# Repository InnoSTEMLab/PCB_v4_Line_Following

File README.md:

# PCB_v5_Line_Following

## Updates:
- New IC Atemga328pa -> Atemga32u4. Takes D+ and D- from usb no need for usb to uart controller
- Motor connectors moved in one section of the board
- Trace fixed for switch that was keeping motor controller on all the time. Motors will be off when usb c connected only.
- Power conversion only happens in one part of the pcb
- USB C footprint updated to current part we have previosuily ordered. No more issues soldering them.
- Decoupling capacitors added to motor driver and termination resistors to USB C data lines

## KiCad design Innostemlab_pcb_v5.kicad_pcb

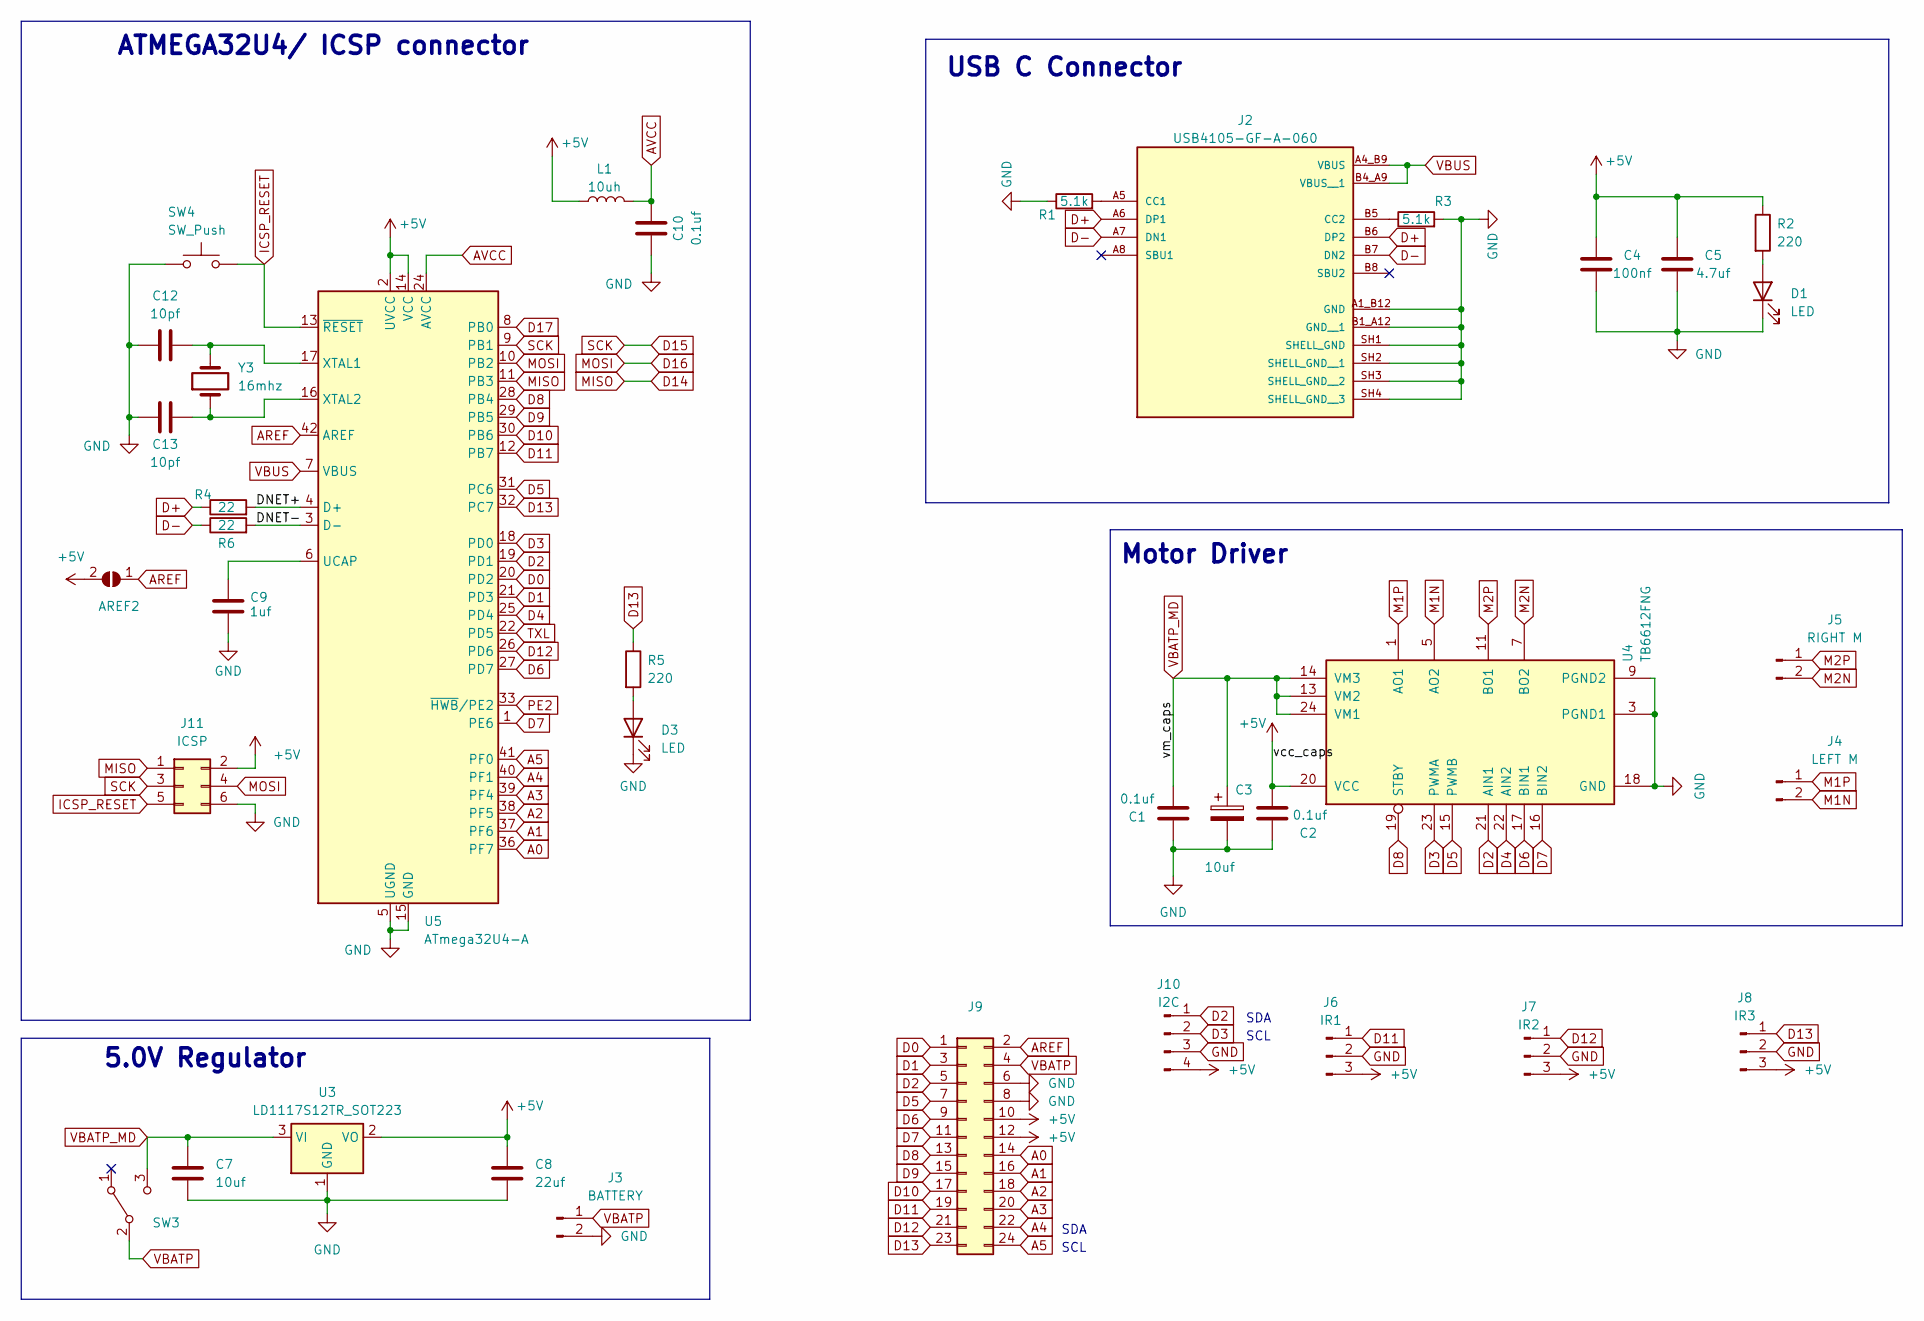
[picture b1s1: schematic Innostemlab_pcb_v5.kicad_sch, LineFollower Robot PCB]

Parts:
AREF2: SolderJumper_2_Open; SolderJumper-2_P1.3mm_Open_RoundedPad1.0x1.5mm
C1, C2, C10: 0.1uf; C_0805_2012Metric_Pad1.18x1.45mm_HandSolder
C3: 10uf; CP_EIA-3528-12_Kemet-T
C4: 100nf; C_0805_2012Metric_Pad1.18x1.45mm_HandSolder
C5: 4.7uf; C_0805_2012Metric_Pad1.18x1.45mm_HandSolder
C7: 10uf; C_0805_2012Metric_Pad1.18x1.45mm_HandSolder
C8: 22uf; C_0805_2012Metric_Pad1.18x1.45mm_HandSolder
C9: 1uf; C_0805_2012Metric_Pad1.18x1.45mm_HandSolder
C12, C13: 10pf; C_0805_2012Metric_Pad1.18x1.45mm_HandSolder
D1, D3: LED; LED_0805_2012Metric_Pad1.15x1.40mm_HandSolder
J2: USB4105-GF-A-060; GCT_USB4105-GF-A-060; PARTREV B3
J3: BATTERY; JST_EH_B2B-EH-A_1x02_P2.50mm_Vertical
J4: LEFT M; JST_EH_B2B-EH-A_1x02_P2.50mm_Vertical
J5: RIGHT M; JST_EH_B2B-EH-A_1x02_P2.50mm_Vertical
J6: IR1; PinHeader_1x03_P2.54mm_Vertical
J7: IR2; PinHeader_1x03_P2.54mm_Vertical
J8: IR3; PinHeader_1x03_P2.54mm_Vertical
J9: Conn_02x12_Odd_Even; PinHeader_2x12_P2.54mm_Vertical
J10: I2C; PinHeader_1x04_P2.54mm_Vertical
J11: ICSP; PinHeader_2x03_P2.54mm_Vertical
L1: 10uh; L_0805_2012Metric
R1, R3: 5.1k; R_0805_2012Metric_Pad1.20x1.40mm_HandSolder
R2, R5: 220; R_0805_2012Metric_Pad1.20x1.40mm_HandSolder
R4, R6: 22; R_0805_2012Metric_Pad1.20x1.40mm_HandSolder
SW3: SW_SPDT; SW_SLW-121586-5A-D
SW4: SW_Push; SW_TS09-63-25-WT-260-SMT-TR
U3: LD1117S12TR_SOT223; SOT-223-3_TabPin2
U4: TB6612FNG; SSOP-24_5.3x8.2mm_P0.65mm
U5: ATmega32U4-A; TQFP-44_10x10mm_P0.8mm
Y3: 16mhz; Crystal_HC49-4H_Vertical

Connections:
+5V: AREF2.2 (B), C2.2, C4.2, C5.2, C8.1, J6.3, J7.3, J8.3, J9.10, J9.12, J10.4, J11.2, L1.1, R2.1, U3.2 (VO), U4.20 (VCC), U5.2 (UVCC), U5.14 (VCC), U5.34 (VCC)
/DNET+: R4.2, U5.4 (D+)
/DNET-: R6.2, U5.3 (D-)
A0: J9.14, U5.36 (PF7)
A1: J9.16, U5.37 (PF6)
A2: J9.18, U5.38 (PF5)
A3: J9.20, U5.39 (PF4)
A4: J9.22, U5.40 (PF1)
A5: J9.24, U5.41 (PF0)
AREF: AREF2.1 (A), J9.2, U5.42 (AREF)
AVCC: C10.2, L1.2, U5.24 (AVCC), U5.44 (AVCC)
D0: J9.1, U5.20 (PD2)
D1: J9.3, U5.21 (PD3)
D2: J9.5, J10.1, U4.21 (AIN1), U5.19 (PD1)
D3: J10.2, U4.23 (PWMA), U5.18 (PD0)
D4: U4.22 (AIN2), U5.25 (PD4)
D5: J9.7, U4.15 (PWMB), U5.31 (PC6)
D6: J9.9, U4.17 (BIN1), U5.27 (PD7)
D7: J9.11, U4.16 (BIN2), U5.1 (PE6)
D8: J9.13, U4.19 (STBY), U5.28 (PB4)
D9: J9.15, U5.29 (PB5)
D10: J9.17, U5.30 (PB6)
D11: J6.1, J9.19, U5.12 (PB7)
D12: J7.1, J9.21, U5.26 (PD6)
D13: J8.1, J9.23, R5.1, U5.32 (PC7)
D14: J11.1, U5.11 (PB3)
D15: J11.3, U5.9 (PB1)
D16: J11.4, U5.10 (PB2)
D17: U5.8 (PB0)
D+: J2.A6 (DP1), J2.B6 (DP2), R4.1
D-: J2.A7 (DN1), J2.B7 (DN2), R6.1
GND: C1.1, C2.1, C3.2, C4.1, C5.1, C7.2, C8.2, C9.1, C10.1, C12.1, C13.1, D1.1 (K), D3.1 (K), J2.A1_B12 (GND), J2.B1_A12 (GND__1), J2.SH1 (SHELL_GND), J2.SH2 (SHELL_GND__1), J2.SH3 (SHELL_GND__2), J2.SH4 (SHELL_GND__3), J3.2, J6.2, J7.2, J8.2, J9.6, J9.8, J10.3, J11.6, R1.1, R3.2, SW4.1, U3.1 (GND), U4.3 (PGND1), U4.4 (PGND1), U4.9 (PGND2), U4.10 (PGND2), U4.18 (GND), U5.5 (UGND), U5.15 (GND), U5.23 (GND), U5.35 (GND), U5.43 (GND)
ICSP_RESET: J11.5, SW4.2, U5.13 (~RESET)
M1N: J4.2, U4.5 (AO2), U4.6 (AO2)
M1P: J4.1, U4.1 (AO1), U4.2 (AO1)
M2N: J5.2, U4.7 (BO2), U4.8 (BO2)
M2P: J5.1, U4.11 (BO1), U4.12 (BO1)
unnamed: D1.2 (A), R2.2
unnamed: D3.2 (A), R5.2
unnamed: J2.A5 (CC1), R1.2
unnamed: J2.B5 (CC2), R3.1
unnamed: C9.2, U5.6 (UCAP)
unnamed: C12.2, U5.17 (XTAL1), Y3.2
unnamed: C13.2, U5.16 (XTAL2), Y3.1
PE2: U5.33 (~HWB/PE2)
TXL: U5.22 (PD5)
VBATP: J3.1, J9.4, SW3.2 (B)
VBATP_MD: C1.2, C3.1, C7.1, SW3.3 (C), U3.3 (VI), U4.13 (VM2), U4.14 (VM3), U4.24 (VM1)
VBUS: J2.A4_B9 (VBUS), J2.B4_A9 (VBUS__1), U5.7 (VBUS)

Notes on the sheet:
USB C Connector
SCL
SDA
ATMEGA32U4/ ICSP connector
5.0V Regulator
Motor Driver

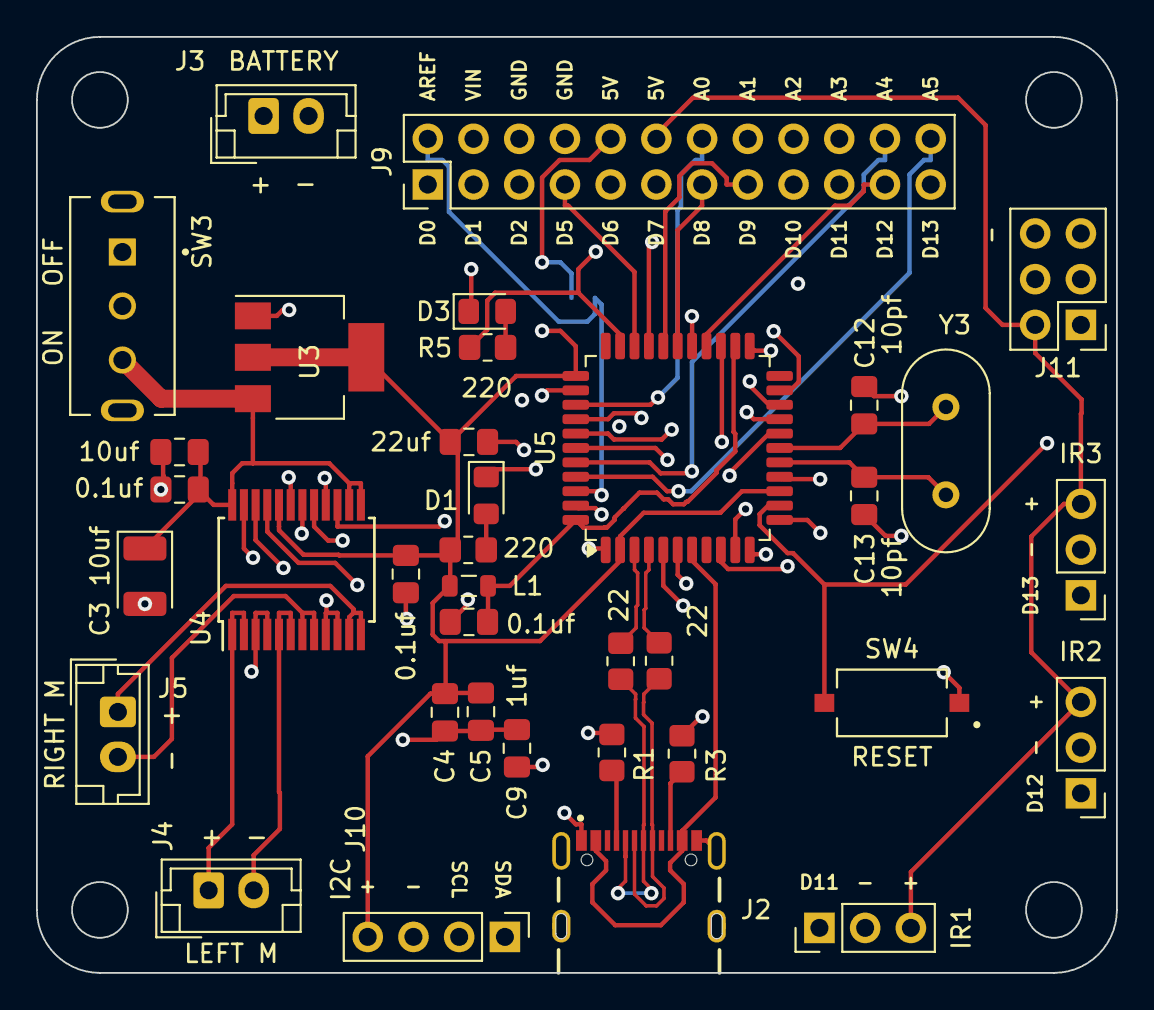
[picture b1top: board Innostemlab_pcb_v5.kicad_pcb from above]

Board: 4 copper layers, 60.0 x 52.0 mm, 37 parts (1 on the bottom side), 46 nets.

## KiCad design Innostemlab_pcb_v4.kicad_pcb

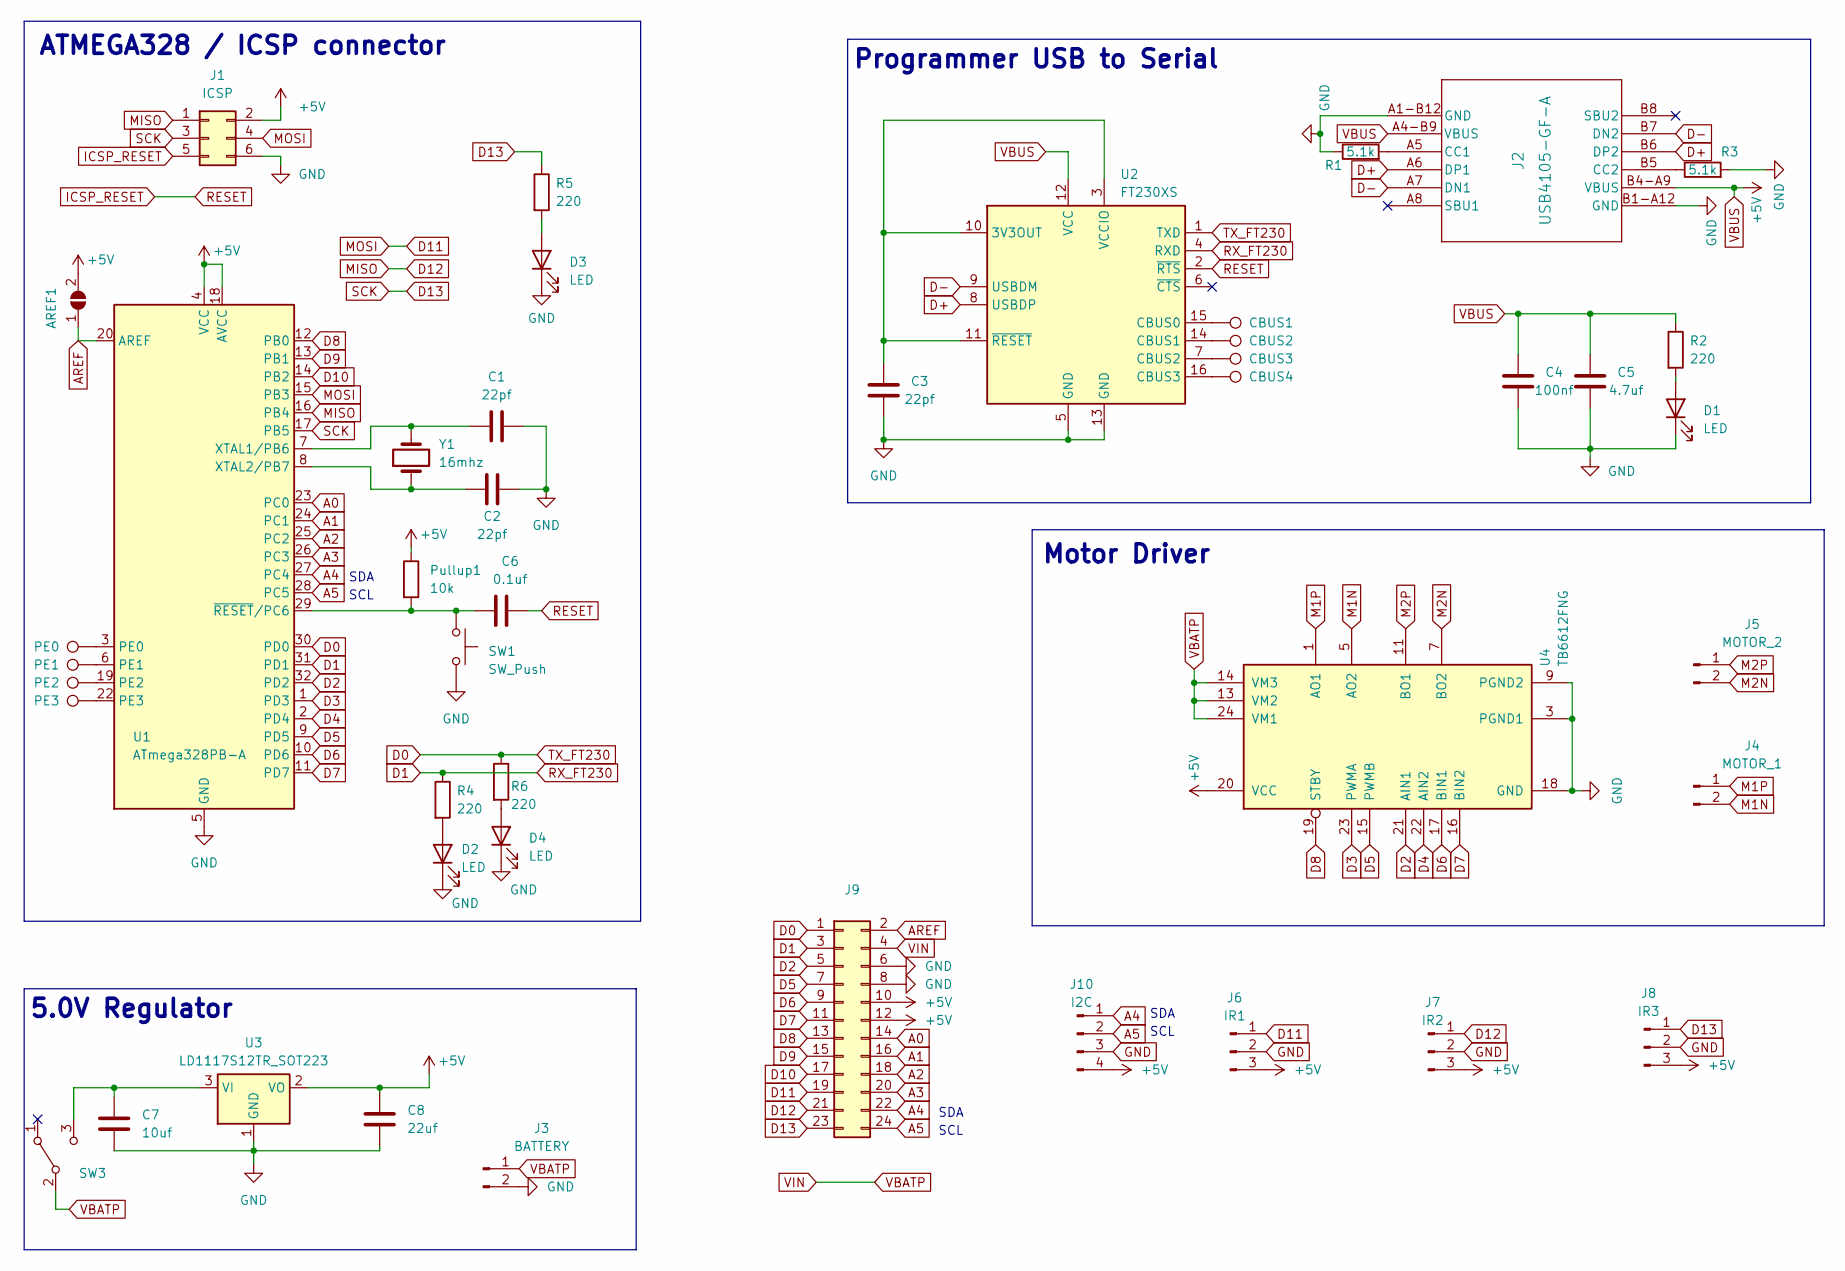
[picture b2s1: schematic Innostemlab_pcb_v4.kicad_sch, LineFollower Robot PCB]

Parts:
AREF1: SolderJumper_2_Open; SolderJumper-2_P1.3mm_Open_RoundedPad1.0x1.5mm
C1, C2, C3: 22pf; C_0805_2012Metric_Pad1.18x1.45mm_HandSolder
C4: 100nf; C_0805_2012Metric_Pad1.18x1.45mm_HandSolder
C5: 4.7uf; C_0805_2012Metric_Pad1.18x1.45mm_HandSolder
C6: 0.1uf; C_0805_2012Metric_Pad1.18x1.45mm_HandSolder
C7: 10uf; C_0805_2012Metric_Pad1.18x1.45mm_HandSolder
C8: 22uf; C_0805_2012Metric_Pad1.18x1.45mm_HandSolder
CBUS1, CBUS2, CBUS3, CBUS4: TestPoint; TestPoint_Pad_D1.5mm
D1, D2, D3, D4: LED; LED_0805_2012Metric_Pad1.15x1.40mm_HandSolder
J1: ICSP; PinHeader_2x03_P2.54mm_Vertical
J2: USB4105-GF-A; USB4105_GCT
J3: BATTERY; JST_EH_B2B-EH-A_1x02_P2.50mm_Vertical
J4: MOTOR_1; JST_EH_B2B-EH-A_1x02_P2.50mm_Vertical
J5: MOTOR_2; JST_EH_B2B-EH-A_1x02_P2.50mm_Vertical
J6: IR1; PinHeader_1x03_P2.54mm_Vertical
J7: IR2; PinHeader_1x03_P2.54mm_Vertical
J8: IR3; PinHeader_1x03_P2.54mm_Vertical
J9: Conn_02x12_Odd_Even; PinHeader_2x12_P2.54mm_Vertical
J10: I2C; PinHeader_1x04_P2.54mm_Vertical
PE0, PE1, PE2, PE3: TestPoint; TestPoint_Pad_D1.5mm
Pullup1: 10k; R_0805_2012Metric_Pad1.20x1.40mm_HandSolder
R1, R3: 5.1k; R_0805_2012Metric_Pad1.20x1.40mm_HandSolder
R2, R4, R5, R6: 220; R_0805_2012Metric_Pad1.20x1.40mm_HandSolder
SW1: SW_Push; SW_TS09-63-25-WT-260-SMT-TR
SW3: SW_SPDT; SW_SLW-121586-5A-D
U1: ATmega328PB-A; TQFP-32_7x7mm_P0.8mm
U2: FT230XS; SSOP-16_3.9x4.9mm_P0.635mm
U3: LD1117S12TR_SOT223; SOT-223-3_TabPin2
U4: TB6612FNG; SSOP-24_5.3x8.2mm_P0.65mm
Y1: 16mhz; Crystal_HC49-4H_Vertical

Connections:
A0: J9.14, U1.23 (PC0)
A1: J9.16, U1.24 (PC1)
A2: J9.18, U1.25 (PC2)
A3: J9.20, U1.26 (PC3)
A4: J9.22, J10.1, U1.27 (PC4)
A5: J9.24, J10.2, U1.28 (PC5)
AREF: AREF1.1 (A), J9.2, U1.20 (AREF)
D0: J9.1, R6.1, U1.30 (PD0), U2.1 (TXD)
D1: J9.3, R4.1, U1.31 (PD1), U2.4 (RXD)
D2: J9.5, U1.32 (PD2), U4.21 (AIN1)
D3: U1.1 (PD3), U4.23 (PWMA)
D4: U1.2 (PD4), U4.22 (AIN2)
D5: J9.7, U1.9 (PD5), U4.15 (PWMB)
D6: J9.9, U1.10 (PD6), U4.17 (BIN1)
D7: J9.11, U1.11 (PD7), U4.16 (BIN2)
D8: J9.13, U1.12 (PB0), U4.19 (STBY)
D9: J9.15, U1.13 (PB1)
D10: J9.17, U1.14 (PB2)
D11: J1.4, J6.1, J9.19, U1.15 (PB3)
D12: J1.1, J7.1, J9.21, U1.16 (PB4)
D13: J1.3, J8.1, J9.23, R5.1, U1.17 (PB5)
D+: J2.A6 (DP1), J2.B6 (DP2), U2.8 (USBDP)
D-: J2.A7 (DN1), J2.B7 (DN2), U2.9 (USBDM)
GND: C1.2, C2.2, C3.1, C4.1, C5.1, C7.2, C8.2, D1.1 (K), D2.1 (K), D3.1 (K), D4.1 (K), J1.6, J2.A1-B12 (GND), J2.B1-A12 (GND), J3.2, J6.2, J7.2, J8.2, J9.6, J9.8, J10.3, R1.1, R3.2, SW1.2, U1.5 (GND), U1.21 (GND), U2.5 (GND), U2.13 (GND), U3.1 (GND), U4.3 (PGND1), U4.4 (PGND1), U4.9 (PGND2), U4.10 (PGND2), U4.18 (GND)
ICSP_RESET: C6.2, J1.5, U2.2 (~RTS)
M1N: J4.2, U4.5 (AO2), U4.6 (AO2)
M1P: J4.1, U4.1 (AO1), U4.2 (AO1)
M2N: J5.2, U4.7 (BO2), U4.8 (BO2)
M2P: J5.1, U4.11 (BO1), U4.12 (BO1)
unnamed: D1.2 (A), R2.2
unnamed: D2.2 (A), R4.2
unnamed: D3.2 (A), R5.2
unnamed: D4.2 (A), R6.2
unnamed: J2.A5 (CC1), R1.2
unnamed: J2.B5 (CC2), R3.1
unnamed: C7.1, SW3.3 (C), U3.3 (VI)
unnamed: PE0.1, U1.3 (PE0)
unnamed: PE1.1, U1.6 (PE1)
unnamed: PE2.1, U1.19 (PE2)
unnamed: PE3.1, U1.22 (PE3)
unnamed: C1.1, U1.7 (XTAL1/PB6), Y1.2
unnamed: C2.1, U1.8 (XTAL2/PB7), Y1.1
unnamed: C6.1, Pullup1.2, SW1.1, U1.29 (~RESET/PC6)
unnamed: C3.2, U2.3 (VCCIO), U2.10 (3V3OUT), U2.11 (~RESET)
unnamed: CBUS1.1, U2.15 (CBUS0)
unnamed: CBUS2.1, U2.14 (CBUS1)
unnamed: CBUS3.1, U2.7 (CBUS2)
unnamed: CBUS4.1, U2.16 (CBUS3)
VBATP: J3.1, J9.4, SW3.2 (B), U4.13 (VM2), U4.14 (VM3), U4.24 (VM1)
VBUS: AREF1.2 (B), C4.2, C5.2, C8.1, J1.2, J2.A4-B9 (VBUS), J2.B4-A9 (VBUS), J6.3, J7.3, J8.3, J9.10, J9.12, J10.4, Pullup1.1, R2.1, U1.4 (VCC), U1.18 (AVCC), U2.12 (VCC), U3.2 (VO), U4.20 (VCC)

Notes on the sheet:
Programmer USB to Serial
SCL
SDA
ATMEGA328 / ICSP connector
5.0V Regulator
Motor Driver

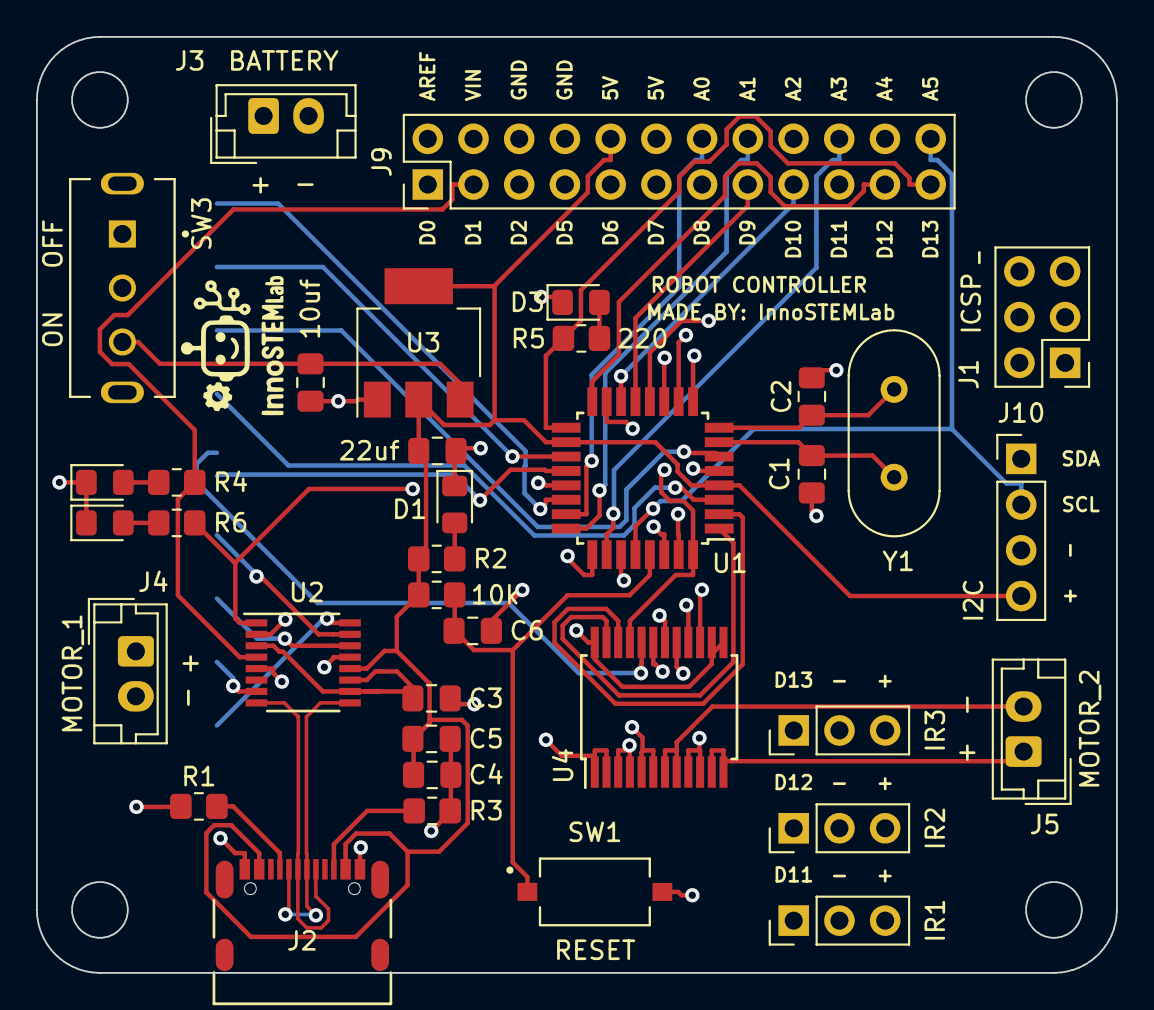
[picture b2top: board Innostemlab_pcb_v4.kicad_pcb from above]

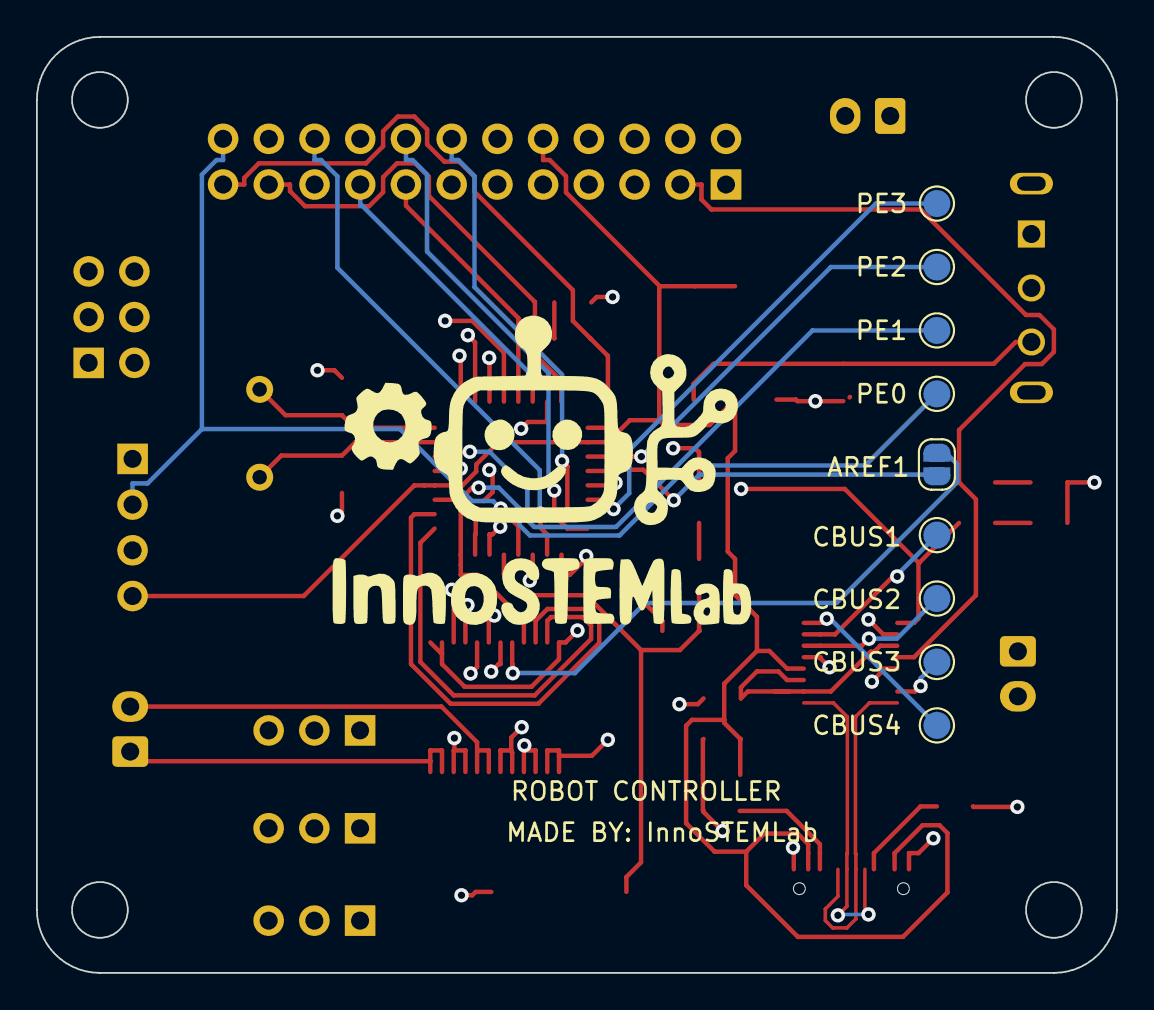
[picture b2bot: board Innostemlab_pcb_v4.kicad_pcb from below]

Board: 4 copper layers, 60.0 x 52.0 mm, 45 parts (9 on the bottom side), 50 nets.

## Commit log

2025-09-25 New changes with atmega32u4 no programmer, and putting all motors in one section
2025-09-25 docs: created a schematic pdf
2025-09-25 docs: added photo
2025-09-25 updated readme photo
2025-10-08 Added caps in TB motor driver, added 22 ohm resistors in usb c data lines, changed part number for AVCC low pass filter, LD1117 datasheet from digikey shows same implementation
2025-10-08 changed label to left and right for motor, the other edits happened in previous commmit
2025-10-14 Added electrolytic cap, changed motor nammmes to left and right
2025-10-14 updaated picture
2025-10-14 added gitignore
2025-10-14 updated vbus and 5v to be seperate so that usb only powers atmega chip. battery required for other sensors and components
2025-10-14 updated picture
